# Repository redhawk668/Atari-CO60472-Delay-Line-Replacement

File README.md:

# Atari CO60472 Delay Line Replacement

# First Draft
This small PCB is a replacement for the proprietary CO60472 Delay Line chip used in the Atari XL series of computers. It is based on schematics found on the AtariAge forums (https://atariage.com/forums/topic/253024-co60472-delay-line/)

Installed in a 600XL:

The little board, once assembled, is piggybacked on top of a 74LS14 Hex Inverter.

# Billing of Materials:
- 1x 74LS14 or 74HC14 Hex Inverter Schmitt Trigger

Resistors:
- R1  : 120R Resistor, 0603
- R2  : 100R Resistor, 0603
- R3  : 120R Resistor, 0603
- R4  : 270R Resistor, 0603
- R5  : 620R Resistor, 0603

Capacitors:
- C1  : 1nF X7R Capacitor, 0603
- C2  : 150pF X7R Capacitor, 0603
- C3  : 30pF X7R Capacitor, 0603

Bend up pins 2,3,5,9,11 and 13, solder the little PCB on top of the 74LS14. Connect pins 1 and 7 to the PCB. 

# Rev. A
This is a rework of the first design. The functionality is still the same, for this design it is not necessary to bend up pins on the the IC and piggybacking the PCB on top of the IC. The IC can now be soldered on top of the PCB, along with the resistors and capacitors. PCB thickness should be 0.6mm.

# Billing of Materials

Billing of materials is the same as the first design.

This is Rev. A installed in a 600XL, fits perfectly:

# Rev. B
A little rework of Rev. A. This is a full SMD design. However, due to space restrictions it has the same form factor as Rev. A. Functionality is still the same. 

# Billing of Materials
- 1x 74LS14 or 74HC14 TSSOP-14 SMD package

Resistors:
- R1  : 120R Resistor, 0603
- R2  : 100R Resistor, 0603
- R3  : 120R Resistor, 0603
- R4  : 270R Resistor, 0603
- R5  : 620R Resistor, 0603

Capacitors:
- C1  : 1nF Ceramic Capacitor, 0603
- C2  : 150pF Ceramic Capacitor, 0603
- C3  : 30pF Ceramic Capacitor, 0603

Machine pin headers (Omron XR2P-3241)

# Rev. C
Another rework, this is a a lot smaller. Everything now fits within the DIP-14 footprint. The Billing of Materials is the same as Rev. B. 

# Top

# Bottom

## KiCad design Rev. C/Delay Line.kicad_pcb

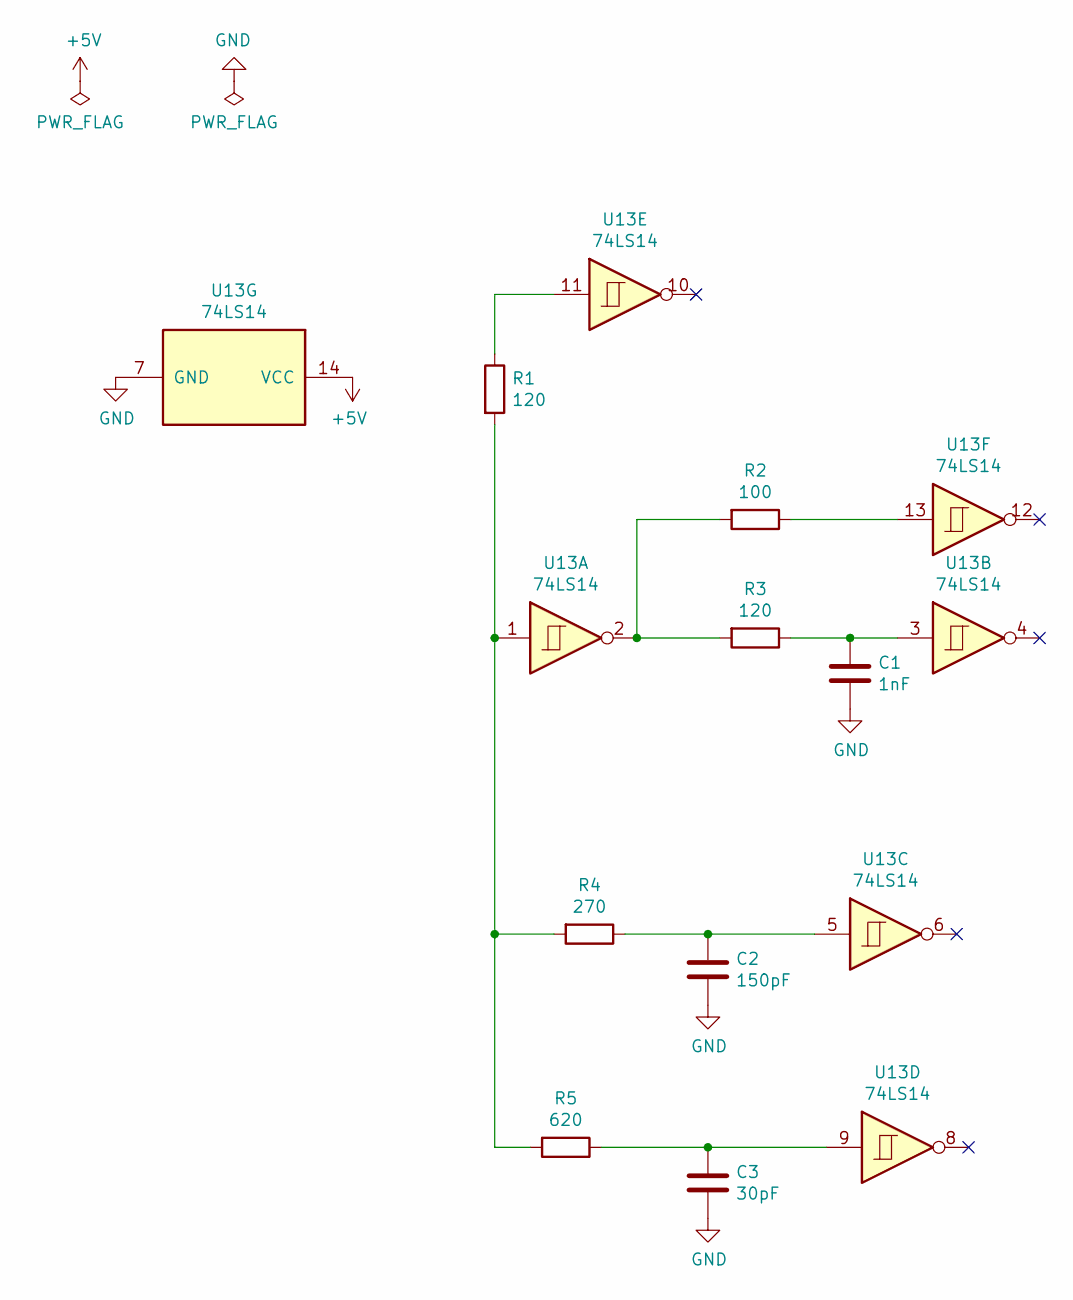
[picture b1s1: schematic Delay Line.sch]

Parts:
C1: 1nF; C_0603_HandSoldering
C2: 150pF; C_0603_HandSoldering
C3: 30pF; C_0603_HandSoldering
R1, R3: 120; R_0603_HandSoldering
R2: 100; R_0603_HandSoldering
R4: 270; R_0603_HandSoldering
R5: 620; R_0603_HandSoldering
U13: 74LS14; TSSOP-14_4.4x5mm_Pitch0.65mm

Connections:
+5V: U13.14 (VCC)
GND: C1.2, C2.2, C3.2, U13.7 (GND)
unnamed: C1.1, R3.1, U13.3
unnamed: C2.1, R4.1, U13.5
unnamed: C3.1, R5.1, U13.9
unnamed: R1.1, U13.11
unnamed: R1.2, R4.2, R5.2, U13.1
unnamed: R2.1, U13.13
unnamed: R2.2, R3.2, U13.2

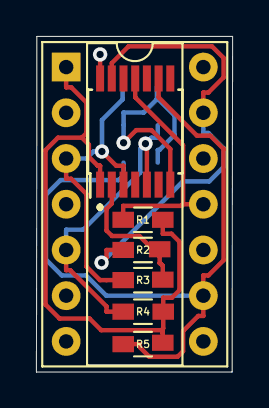
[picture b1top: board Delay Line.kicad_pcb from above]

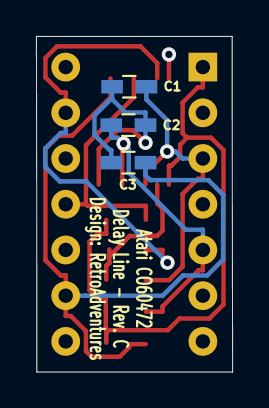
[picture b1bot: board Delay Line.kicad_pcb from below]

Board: 4 copper layers, 10.9 x 18.6 mm, 9 parts (3 on the bottom side), 8 nets.
